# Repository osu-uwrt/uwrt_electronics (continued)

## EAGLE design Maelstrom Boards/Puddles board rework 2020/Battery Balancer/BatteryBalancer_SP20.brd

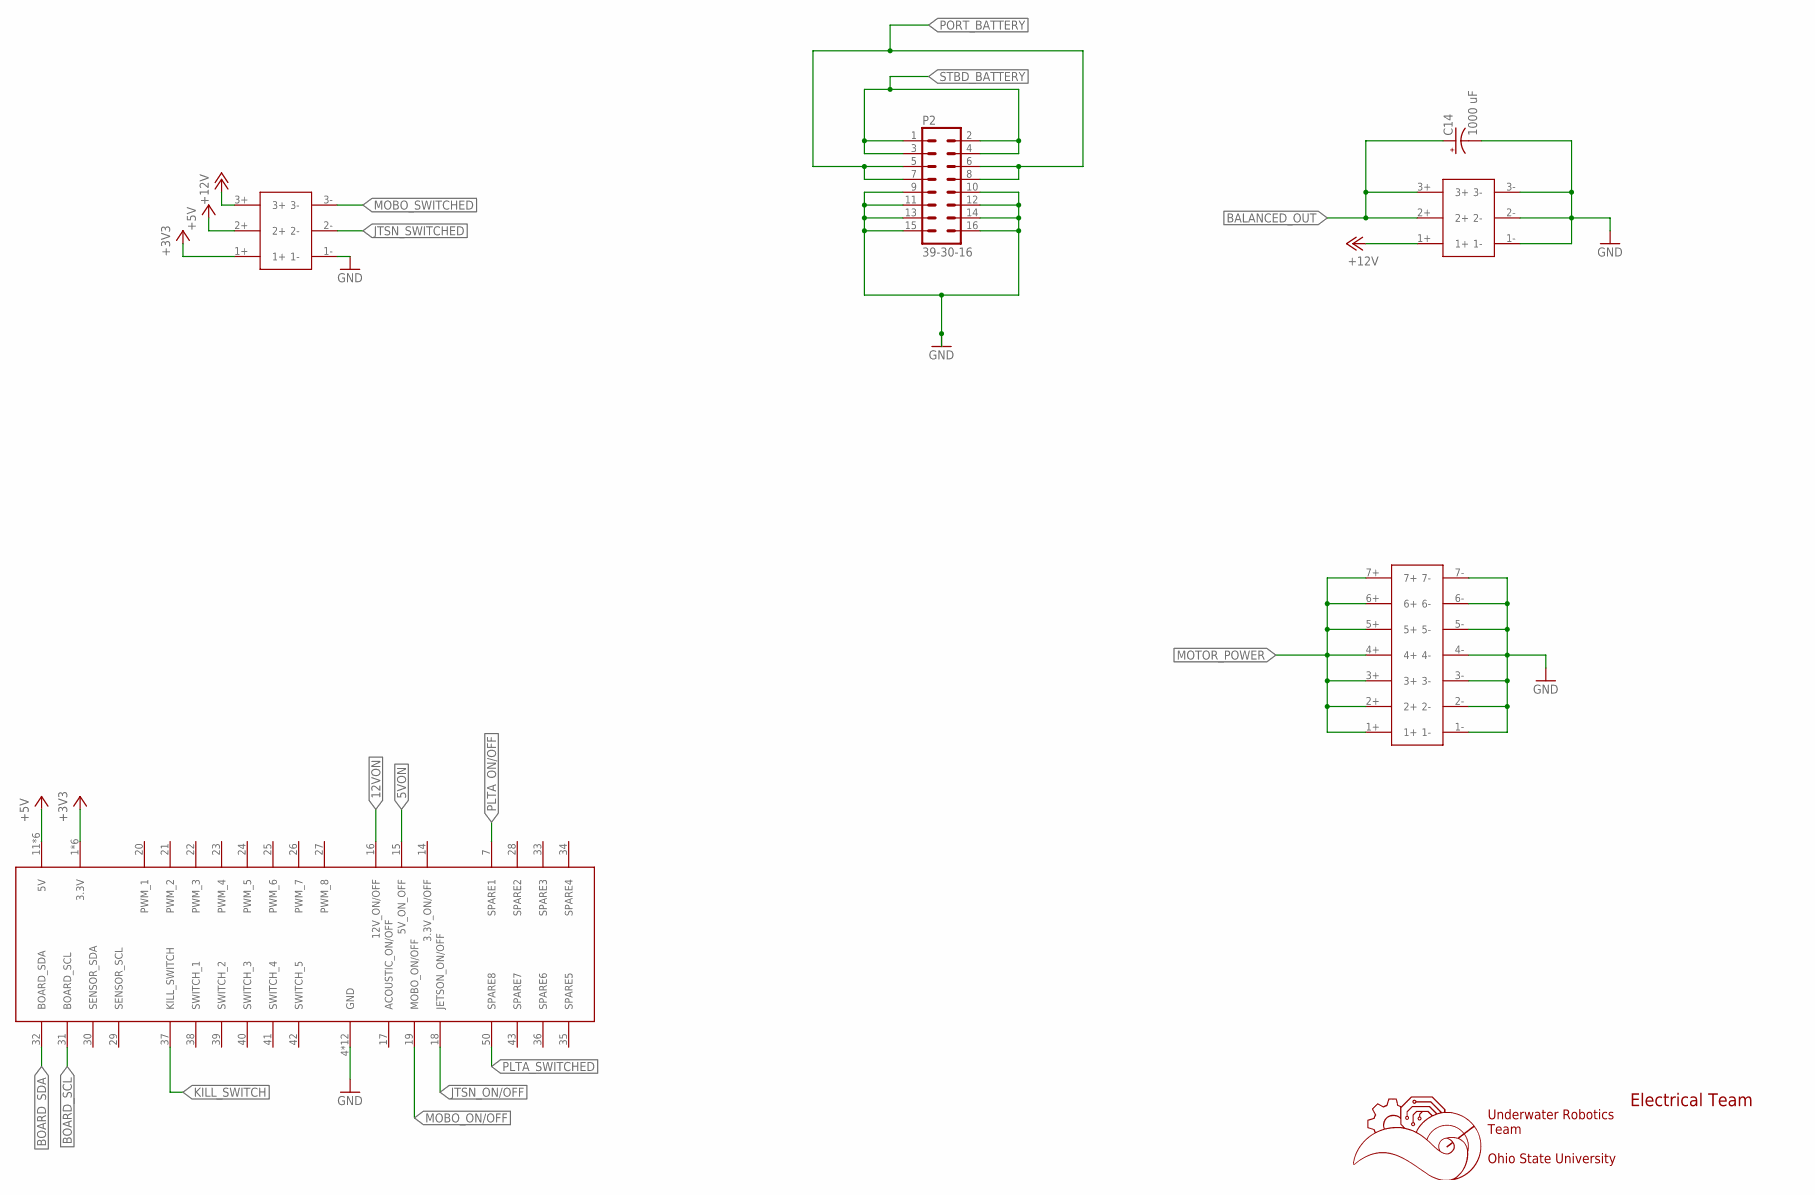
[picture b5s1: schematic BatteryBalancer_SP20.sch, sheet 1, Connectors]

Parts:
C14: 1000 uF; E5-13
P2: 39-30-16; 39-30-?16?
U$1: 5530843-EDGE; 5530843-6-BOARDFINGERS
U$4: 14PIN-VERT; 14PIN_VERT
U$5, U$13: 6PIN-VERT; 6PIN_VERT

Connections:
5VON: U$1.15 (5V_ON_OFF); also elsewhere on the board
12VON: U$1.16 (12V_ON/OFF); also elsewhere on the board
+3V3: U$1.1 (3.3V), U$1.2 (3.3V), U$1.3 (3.3V), U$1.54 (3.3V), U$1.55 (3.3V), U$1.56 (3.3V), U$5.1+; also elsewhere on the board
+5V: U$1.11 (5V), U$1.12 (5V), U$1.13 (5V), U$1.44 (5V), U$1.45 (5V), U$1.46 (5V), U$5.2+; also elsewhere on the board
+12V: U$5.3+, U$13.1+; also elsewhere on the board
BALANCED_OUT: C14.+, U$13.2+, U$13.3+; also elsewhere on the board
BOARD_SCL: U$1.31 (BOARD_SCL); also elsewhere on the board
BOARD_SDA: U$1.32 (BOARD_SDA); also elsewhere on the board
GND: C14.-, P2.9, P2.10, P2.11, P2.12, P2.13, P2.14, P2.15, P2.16, U$1.4 (GND), U$1.5 (GND), U$1.6 (GND), U$1.8 (GND), U$1.9 (GND), U$1.10 (GND), U$1.47 (GND), U$1.48 (GND), U$1.49 (GND), U$1.51 (GND), U$1.52 (GND), U$1.53 (GND), U$4.1-, U$4.2-, U$4.3-, U$4.4-, U$4.5-, U$4.6-, U$4.7-, U$5.1-, U$13.1-, U$13.2-, U$13.3-; also elsewhere on the board
JTSN_ON/OFF: U$1.18 (JETSON_ON/OFF); also elsewhere on the board
JTSN_SWITCHED: U$5.2-; also elsewhere on the board
KILL_SWITCH: U$1.37 (KILL_SWITCH); also elsewhere on the board
MOBO_ON/OFF: U$1.19 (MOBO_ON/OFF); also elsewhere on the board
MOBO_SWITCHED: U$5.3-; also elsewhere on the board
MOTOR_POWER: U$4.1+, U$4.2+, U$4.3+, U$4.4+, U$4.5+, U$4.6+, U$4.7+; also elsewhere on the board
PLTA_ON/OFF: U$1.7 (SPARE1); also elsewhere on the board
PLTA_SWITCHED: U$1.50 (SPARE8); also elsewhere on the board
PORT_BATTERY: P2.5, P2.6, P2.7, P2.8; also elsewhere on the board
STBD_BATTERY: P2.1, P2.2, P2.3, P2.4; also elsewhere on the board

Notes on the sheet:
Underwater Robotics Team Ohio State University
Electrical Team

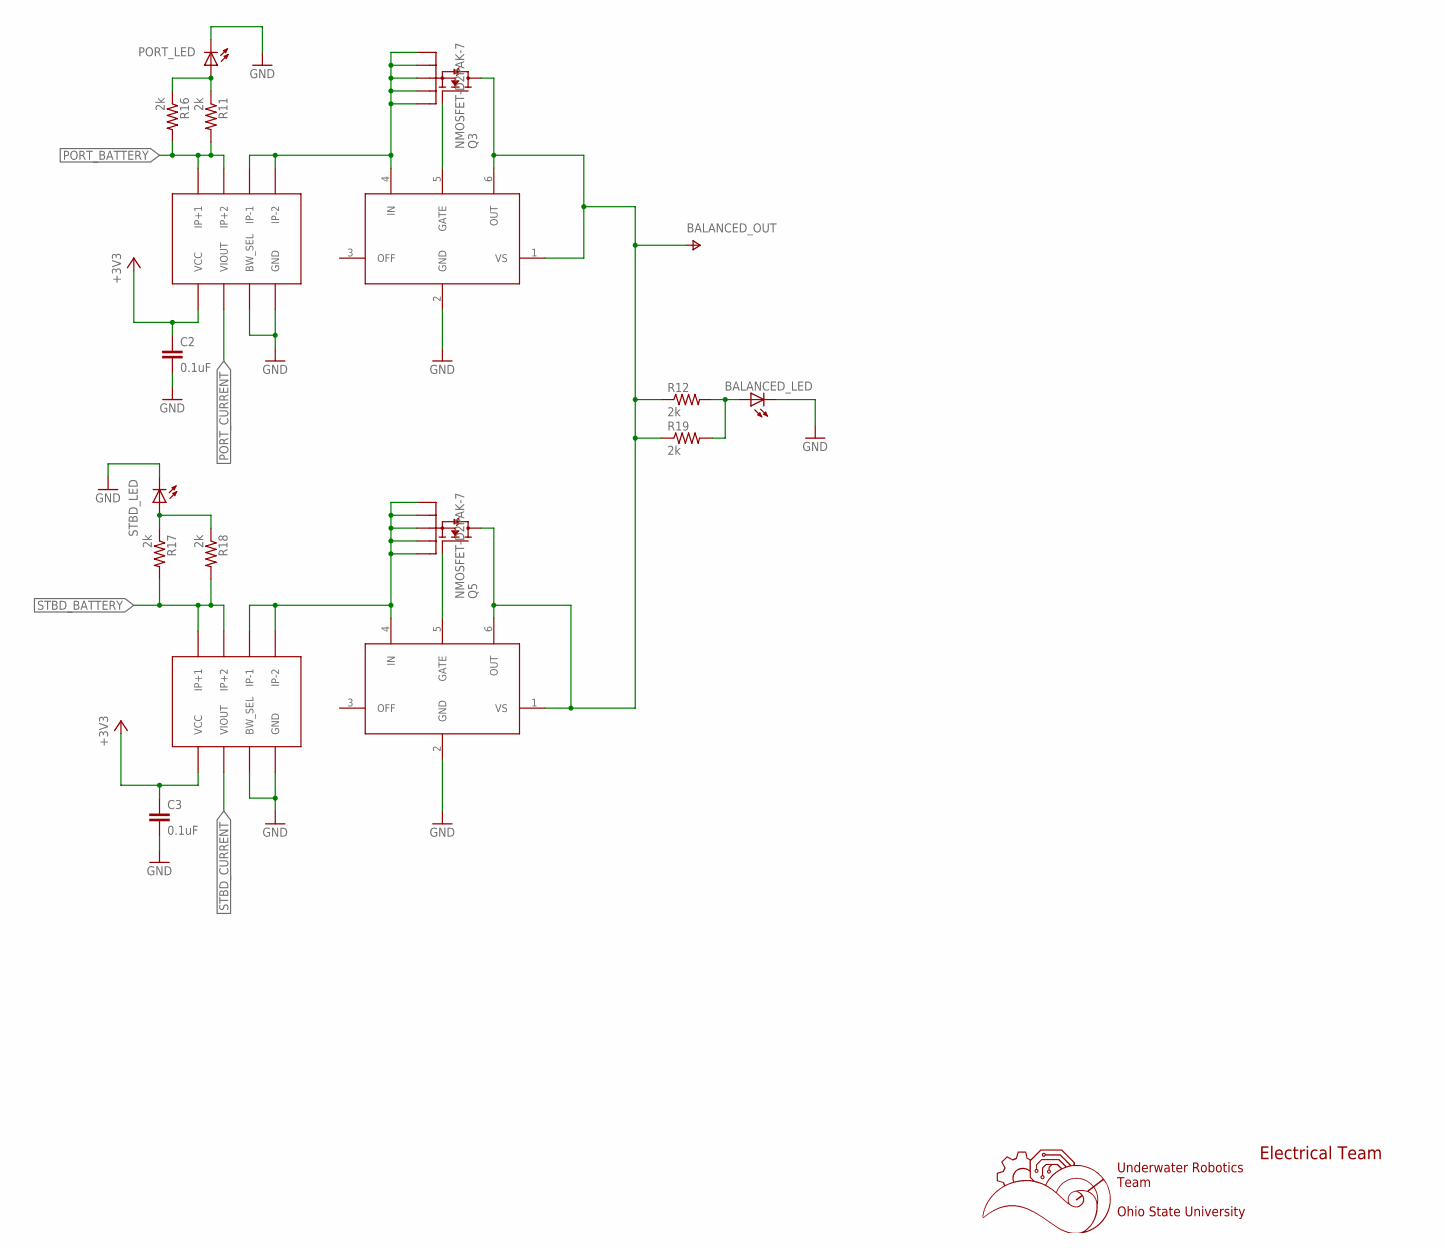
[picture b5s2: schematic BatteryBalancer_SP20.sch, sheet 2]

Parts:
BALANCED_LED: LEDCHIP-LED0603; CHIP-LED0603
C2, C3: 0.1uF; C0603
PORT_LED: LEDCHIP-LED0603; CHIP-LED0603
Q3, Q5: NMOSFET-D2PAK-7; D2PAK-7
R11, R12, R16, R17, R18, R19: 2k; R0603
STBD_LED: LEDCHIP-LED0603; CHIP-LED0603
U$2, U$3: LM5050
U$6, U$7: ACS722; SOIC-8

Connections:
+3V3: C2.1, C3.1, U$6.VCC, U$7.VCC; also elsewhere on the board
BALANCED_OUT: Q3.D, Q5.D, R12.1, R19.1, U$2.1 (VS), U$2.6 (OUT), U$3.1 (VS), U$3.6 (OUT); also elsewhere on the board
GND: BALANCED_LED.C, C2.2, C3.2, PORT_LED.C, STBD_LED.C, U$2.2 (GND), U$3.2 (GND), U$6.BW_SEL, U$6.GND, U$7.BW_SEL, U$7.GND; also elsewhere on the board
unnamed: Q3.S1, Q3.S2, Q3.S3, Q3.S4, Q3.S5, U$2.4 (IN), U$6.IP-1, U$6.IP-2
unnamed: Q3.G, U$2.5 (GATE)
unnamed: Q5.G, U$3.5 (GATE)
unnamed: PORT_LED.A, R11.1, R16.1
unnamed: R17.1, R18.1, STBD_LED.A
unnamed: BALANCED_LED.A, R12.2, R19.2
PORT_BATTERY: R11.2, R16.2, U$6.IP+1, U$6.IP+2; also elsewhere on the board
PORT_CURRENT: U$6.VIOUT; also elsewhere on the board
SOURCE: Q5.S1, Q5.S2, Q5.S3, Q5.S4, Q5.S5, U$3.4 (IN), U$7.IP-1, U$7.IP-2
STBD_BATTERY: R17.2, R18.2, U$7.IP+1, U$7.IP+2; also elsewhere on the board
STBD_CURRENT: U$7.VIOUT; also elsewhere on the board

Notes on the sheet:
Underwater Robotics Team Ohio State University
Electrical Team

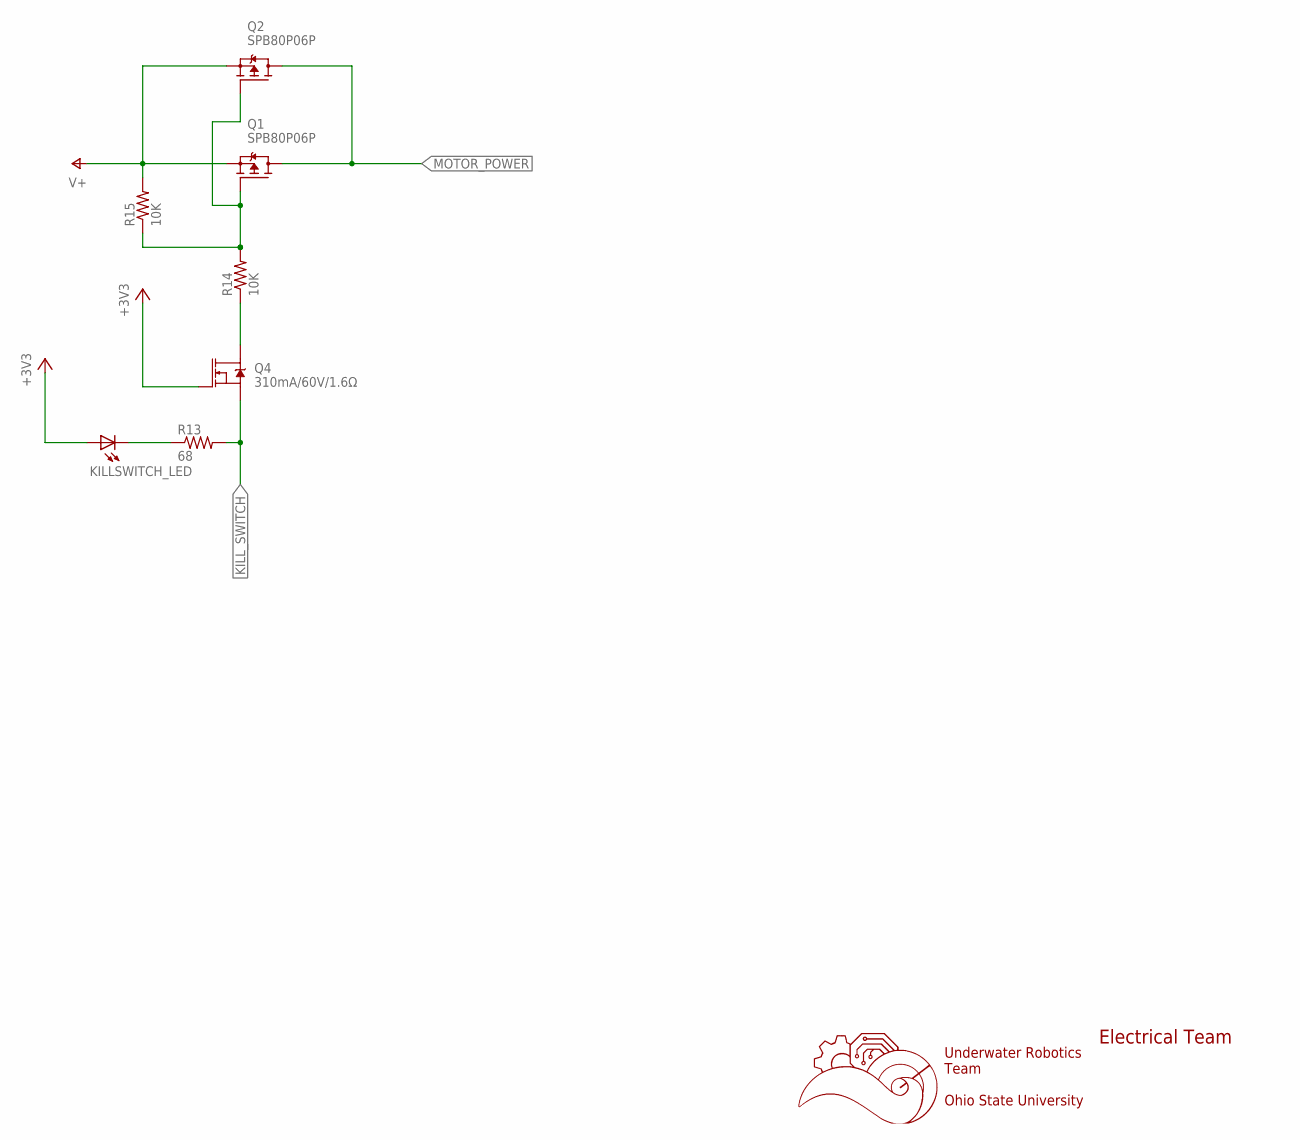
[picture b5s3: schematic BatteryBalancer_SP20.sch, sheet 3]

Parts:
KILLSWITCH_LED: LEDCHIP-LED0603; CHIP-LED0603
Q1, Q2: SPB80P06P; TO263
Q4: 310mA/60V/1.6Ω; SOT323
R13: 68; R0603
R14, R15: 10K; R0603

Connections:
+3V3: KILLSWITCH_LED.A, Q4.1 (G); also elsewhere on the board
BALANCED_OUT: Q1.2 (S), Q2.2 (S), R15.2; also elsewhere on the board
KILL_SWITCH: Q4.2 (S), R13.2; also elsewhere on the board
MOTOR_POWER: Q1.3 (D), Q2.3 (D); also elsewhere on the board
unnamed: Q4.3 (D), R14.1
unnamed: Q1.1 (G), Q2.1 (G), R14.2, R15.1
unnamed: KILLSWITCH_LED.C, R13.1

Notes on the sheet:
Underwater Robotics Team Ohio State University
Electrical Team

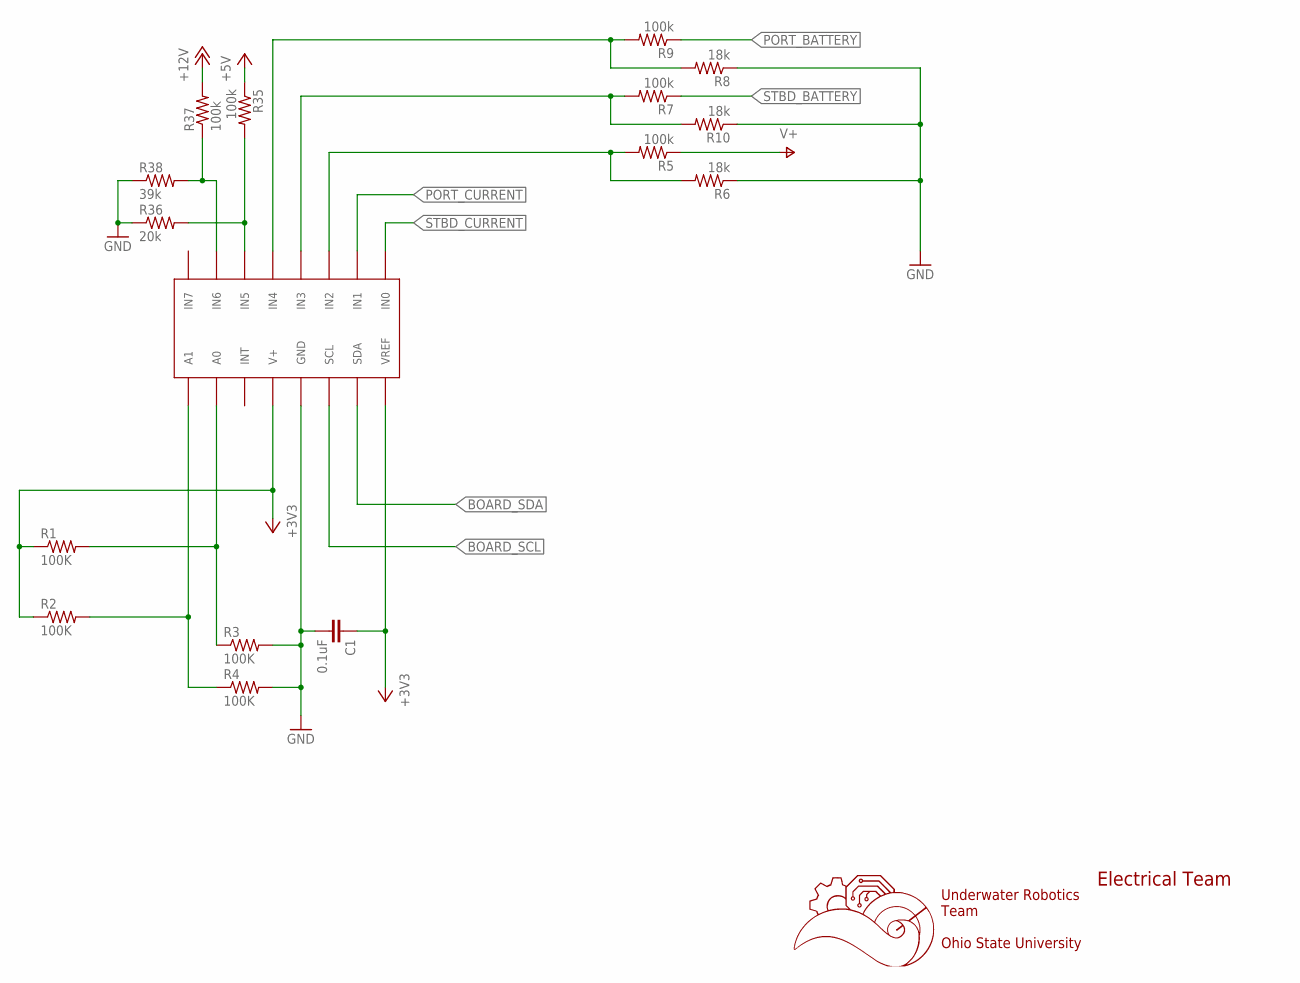
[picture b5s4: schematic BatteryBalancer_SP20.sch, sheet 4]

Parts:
C1: 0.1uF; C0603
R1, R2, R3, R4: 100K; R0603
R5, R7, R9, R35, R37: 100k; R0603
R6, R8, R10: 18k; R0603
R36: 20k; R0603
R38: 39k; R0603
U$12: ADC128D818; TSSOP-16

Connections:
+3V3: C1.1, R1.1, R2.1, U$12.V+, U$12.VREF; also elsewhere on the board
+5V: R35.1; also elsewhere on the board
+12V: R37.2; also elsewhere on the board
BALANCED_OUT: R5.1; also elsewhere on the board
BOARD_SCL: U$12.SCL; also elsewhere on the board
BOARD_SDA: U$12.SDA; also elsewhere on the board
GND: C1.2, R3.2, R4.2, R6.1, R8.1, R10.1, R36.1, R38.1, U$12.GND; also elsewhere on the board
unnamed: R2.2, R4.1, U$12.A1
unnamed: R1.2, R3.1, U$12.A0
unnamed: R7.2, R10.2, U$12.IN3
unnamed: R8.2, R9.2, U$12.IN4
unnamed: R5.2, R6.2, U$12.IN2
unnamed: R37.1, R38.2, U$12.IN6
unnamed: R35.2, R36.2, U$12.IN5
PORT_BATTERY: R9.1; also elsewhere on the board
PORT_CURRENT: U$12.IN1; also elsewhere on the board
STBD_BATTERY: R7.1; also elsewhere on the board
STBD_CURRENT: U$12.IN0; also elsewhere on the board

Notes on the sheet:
Underwater Robotics Team Ohio State University
Electrical Team

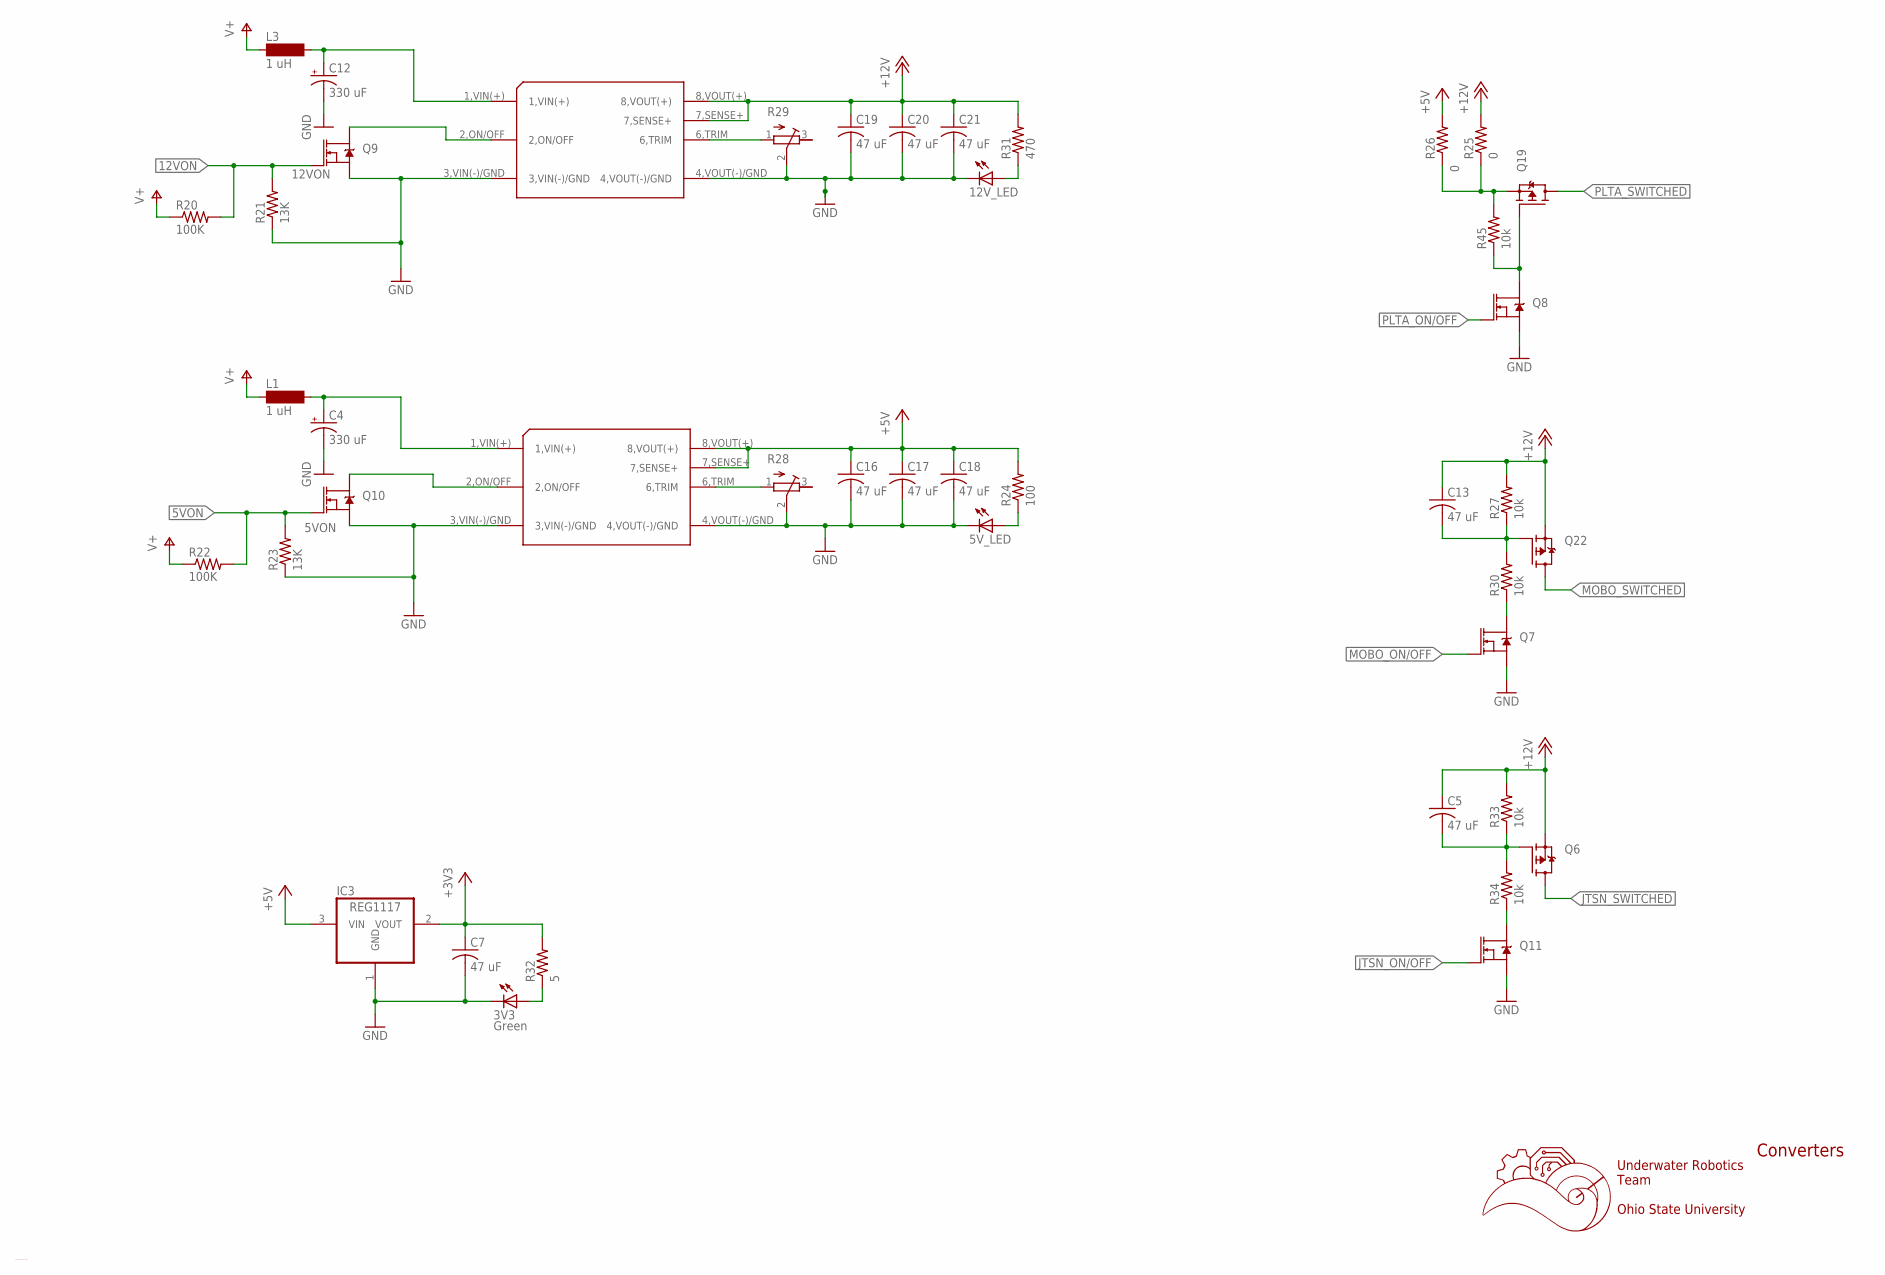
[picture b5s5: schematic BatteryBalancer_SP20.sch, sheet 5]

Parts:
3V3: Green; CHIPLED_0603
5VCONVERTER, 12VCONVERTER: CONVERTER
5V_LED, 12V_LED: LEDCHIPLED_0603; CHIPLED_0603
C4, C12: 330 uF; E5-10,5
C5, C7, C13, C16, C17, C18, C19, C20, C21: 47 uF; C1206K
IC3: REG1117; SOT223
L1, L3: 1 uH; MS85
Q6, Q19, Q22: FDD4141TO252; TO252
Q7, Q8, Q9, Q10, Q11: MOSFET-NCH-AO3404A; SOT23-3
R20, R22: 100K; R0603
R21, R23: 13K; R0603
R24: 100; R0603
R25, R26: 0; M2309
R27, R30, R33, R34, R45: 10k; R0603
R28, R29: R-TRIMM3103; RTRIM3103
R31: 470; R0603
R32: 5; R0603

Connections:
5VON: Q10.1 (G), R22.2, R23.2; also elsewhere on the board
12VON: Q9.1 (G), R20.2, R21.2; also elsewhere on the board
+3V3: C7.1, IC3.2 (VOUT), R32.2; also elsewhere on the board
+5V: 5VCONVERTER.7,SENSE+, 5VCONVERTER.8,VOUT(+), C16.1, C17.1, C18.1, IC3.3 (VIN), R24.2, R26.2; also elsewhere on the board
+12V: 12VCONVERTER.7,SENSE+, 12VCONVERTER.8,VOUT(+), C5.1, C13.1, C19.1, C20.1, C21.1, Q6.2 (S), Q22.2 (S), R25.2, R27.2, R31.2, R33.2; also elsewhere on the board
BALANCED_OUT: L1.1, L3.1, R20.1, R22.1; also elsewhere on the board
GND: 3V3.C, 5VCONVERTER.3,VIN(-)/GND, 5VCONVERTER.4,VOUT(-)/GND, 5V_LED.C, 12VCONVERTER.3,VIN(-)/GND, 12VCONVERTER.4,VOUT(-)/GND, 12V_LED.C, C4.-, C7.2, C12.-, C16.2, C17.2, C18.2, C19.2, C20.2, C21.2, IC3.1 (GND), Q7.2 (S), Q8.2 (S), Q9.2 (S), Q10.2 (S), Q11.2 (S), R21.1, R23.1, R28.2 (S), R29.2 (S); also elsewhere on the board
JTSN_ON/OFF: Q11.1 (G); also elsewhere on the board
JTSN_SWITCHED: Q6.3 (D); also elsewhere on the board
MOBO_ON/OFF: Q7.1 (G); also elsewhere on the board
MOBO_SWITCHED: Q22.3 (D); also elsewhere on the board
unnamed: 12VCONVERTER.6,TRIM, R29.1 (A)
unnamed: 5VCONVERTER.6,TRIM, R28.1 (A)
unnamed: C13.2, Q22.1 (G), R27.1, R30.2
unnamed: 12VCONVERTER.2,ON/OFF, Q9.3 (D)
unnamed: 5VCONVERTER.2,ON/OFF, Q10.3 (D)
unnamed: Q7.3 (D), R30.1
unnamed: Q19.2 (S), R25.1, R26.1, R45.2
unnamed: Q8.3 (D), Q19.1 (G), R45.1
unnamed: 12VCONVERTER.1,VIN(+), C12.+, L3.2
unnamed: 5VCONVERTER.1,VIN(+), C4.+, L1.2
unnamed: 5V_LED.A, R24.1
unnamed: C5.2, Q6.1 (G), R33.1, R34.2
unnamed: 12V_LED.A, R31.1
unnamed: 3V3.A, R32.1
unnamed: Q11.3 (D), R34.1
PLTA_ON/OFF: Q8.1 (G); also elsewhere on the board
PLTA_SWITCHED: Q19.3 (D); also elsewhere on the board

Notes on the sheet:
C:/Users/blain/Downloads/Black and White.bmp
Underwater Robotics Team Ohio State University
Converters

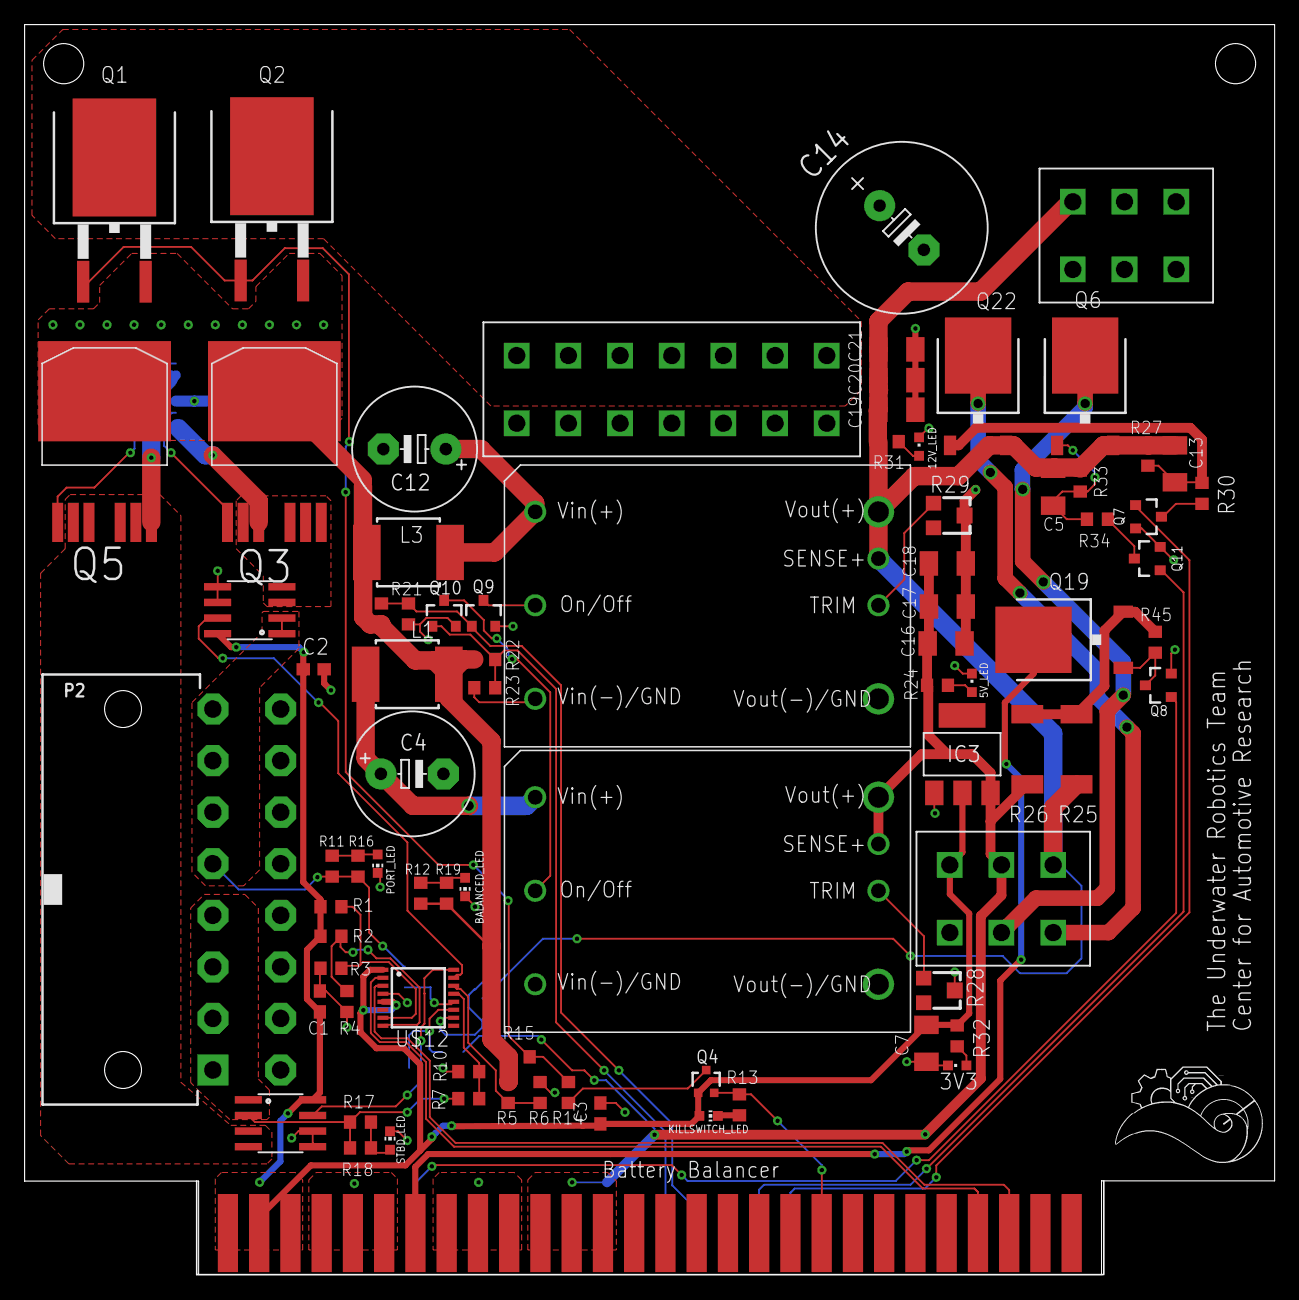
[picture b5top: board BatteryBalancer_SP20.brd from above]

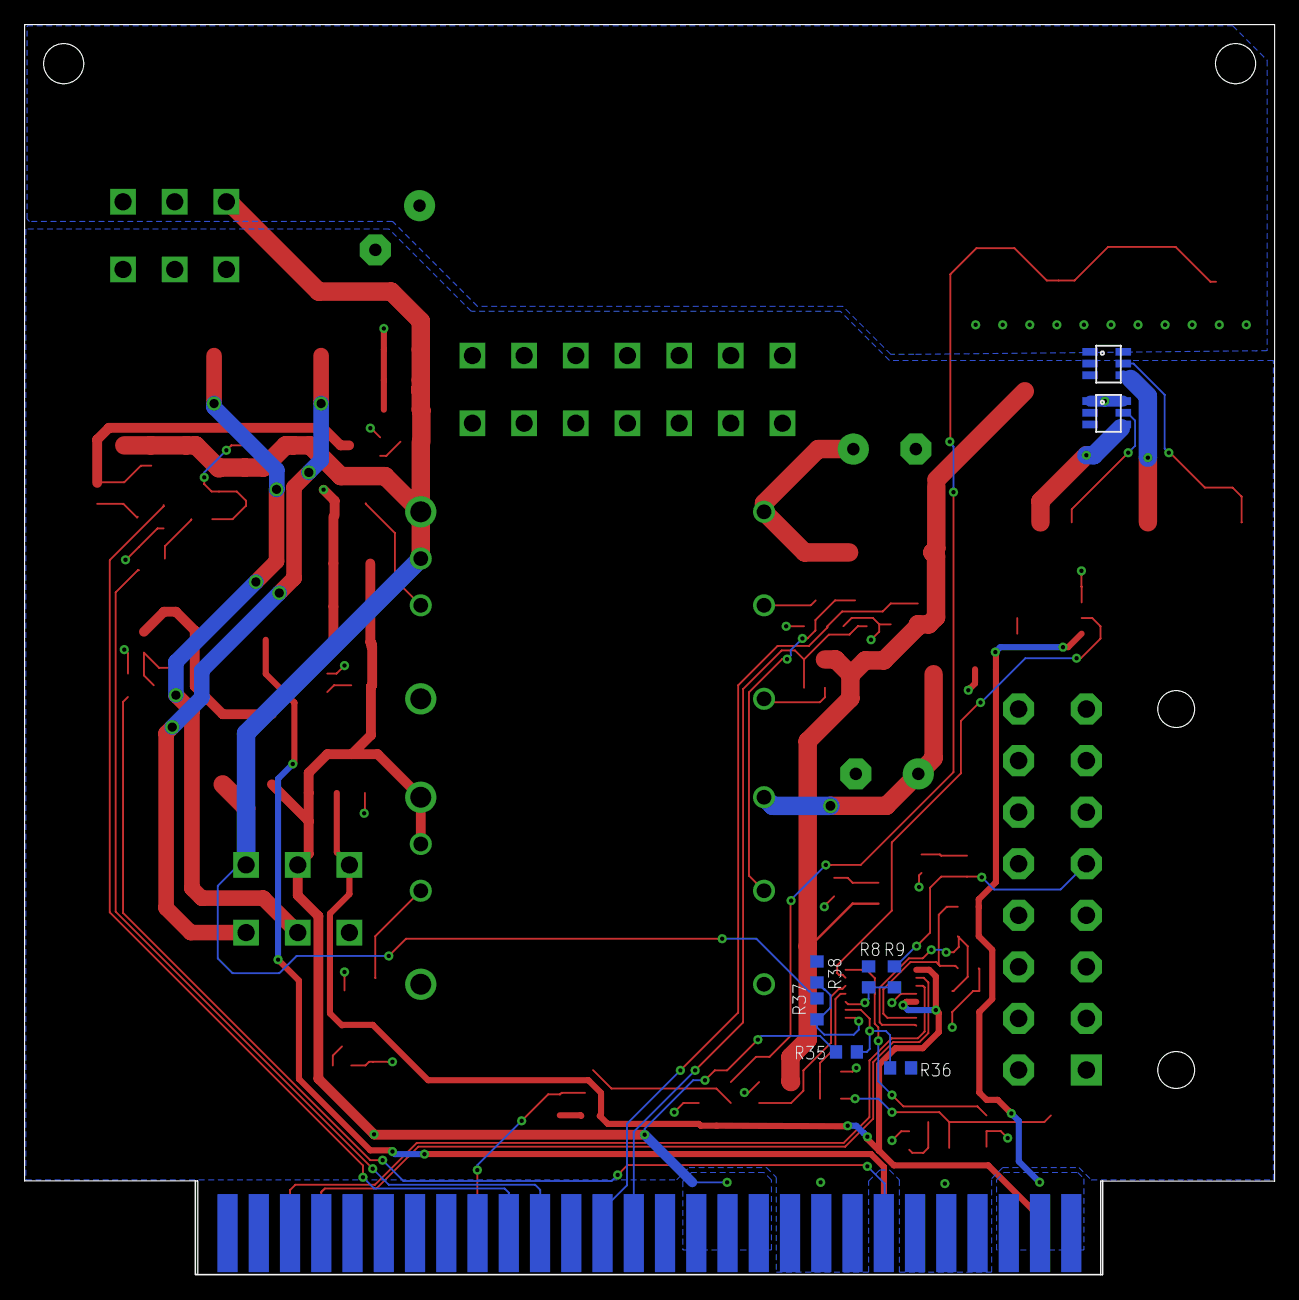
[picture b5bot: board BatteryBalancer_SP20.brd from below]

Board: 2 copper layers, 101.6 x 101.6 mm, 89 parts (8 on the bottom side), 53 nets.
